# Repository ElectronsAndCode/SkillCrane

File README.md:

This is a schematic diagram with circuit explanations for the Benton Big Choice/Action Crane claw games.

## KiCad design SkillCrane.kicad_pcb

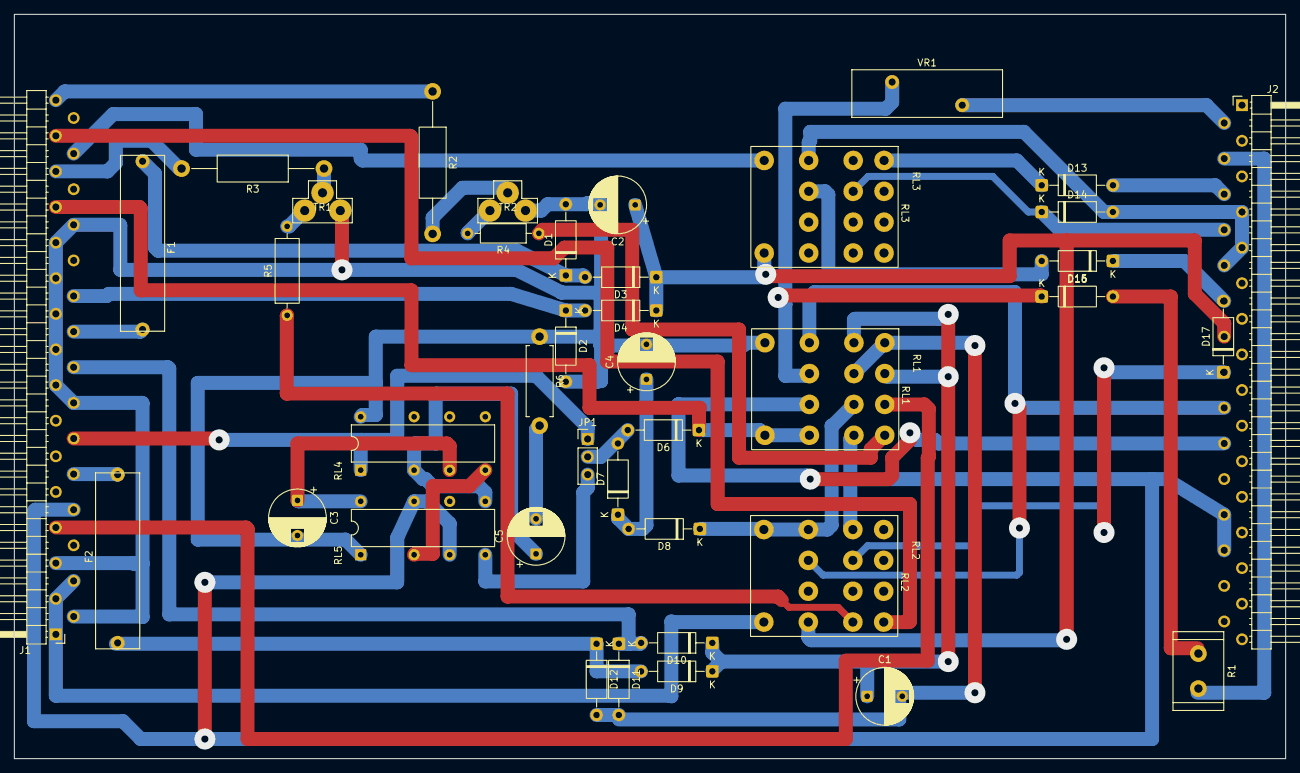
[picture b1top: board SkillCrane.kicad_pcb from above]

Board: 2 copper layers, 181.4 x 106.2 mm, 40 parts (0 on the bottom side), 46 nets.

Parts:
C1, C2, C3, C4: CP_Radial_D8.0mm_P5.00mm
C5: 220uF/25V; CP_Radial_D8.0mm_P5.00mm
D1, D2, D3, D4, D6, D7, D8, D9, D10, D11, D12, D16: D; D_A-405_P10.16mm_Horizontal
D13, D14, D15, D17: D_A-405_P10.16mm_Horizontal
F1: 24V 1A; Fuse
F2: 48V 1A; Fuse
J1: PanelPin; Connector
J2: CabinetPin; Connector
JP1: #COINS; PinHeader_1x03_P2.54mm_Vertical
R1: GRAB STRENGTH; R_Radial_Power_L11.0mm_W7.0mm_P5.00mm
R2, R3: R_Axial_DIN0411_L9.9mm_D3.6mm_P20.32mm_Horizontal
R4: R_Axial_DIN0207_L6.3mm_D2.5mm_P10.16mm_Horizontal
R5: R_Axial_DIN0309_L9.0mm_D3.2mm_P12.70mm_Horizontal
R6: 15K; R_Axial_DIN0411_L9.9mm_D3.6mm_P12.70mm_Horizontal
RL1, RL2, RL3: Relay; PY4-Omron
RL4, RL5: Relay; G2VN
TR1: ZW; Triac
TR2: VW; Triac
VR1: Varistor; RV_Disc_D21.5mm_W6.8mm_P10mm

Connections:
+24V: C2.1, D3.1 (K), D4.1 (K), J2.14, RL2.9, RL3.14
GND: C2.2, C3.2, C4.2, D1.2 (A), D2.2 (A), J1.2, J1.5, J1.14, J1.15, J1.17, J1.19, J1.21, J1.23, J1.24, R6.1, RL1.13, RL4.8, RL5.1, TR1.1 (A1), TR2.1 (A1)
unnamed: C3.1, RL4.3, RL5.8
unnamed: C5.1, RL4.2, RL5.5
unnamed: C5.2, R6.2
unnamed: D1.1 (K), D3.2 (A), F1.1
unnamed: D2.1 (K), D4.2 (A), J1.20
unnamed: D6.2 (A), D7.2 (A), JP1.2 (C)
unnamed: D6.1 (K), J1.25, RL1.9, RL1.14
unnamed: C4.1, D7.1 (K), D8.2 (A)
unnamed: D8.1 (K), RL1.6, RL2.12, RL2.13
unnamed: D10.2 (A), D11.1 (K), J1.16
unnamed: C1.1, D9.1 (K), D10.1 (K), RL1.3, RL1.8
unnamed: C1.2, D11.2 (A), D12.2 (A), RL1.4, RL1.7
unnamed: D9.2 (A), D12.1 (K), F2.1
unnamed: D13.2 (A), J2.6
unnamed: D13.1 (K), RL3.4
unnamed: D14.2 (A), J2.7, J2.9, J2.10, RL3.12
unnamed: D14.1 (K), J2.8, RL3.7
unnamed: D15.2 (A), RL3.11
unnamed: D15.1 (K), D17.2 (A), J2.12
unnamed: D16.2 (A), R1.1
unnamed: D16.1 (K), RL1.11, VR1.2
unnamed: D17.1 (K), J2.16, RL2.7
unnamed: F2.2, J1.10
unnamed: F1.2, J1.18
unnamed: J1.28, RL3.13
unnamed: J1.8, J2.24, J2.26, RL1.5, RL2.8, RL5.3, RL5.7
unnamed: J1.12, JP1.1 (A), RL4.1
unnamed: J1.27, R3.2
unnamed: J1.7, RL1.2
unnamed: J1.29, RL2.1
unnamed: J1.31, R2.1
unnamed: J1.1, J1.3, J1.4, RL2.14
unnamed: J2.20, RL1.10
unnamed: J2.18, RL1.12, RL2.11
unnamed: J2.2, VR1.1
unnamed: J2.4, R1.2
unnamed: JP1.3 (B), RL5.4
unnamed: R4.1, RL1.1
unnamed: R5.1, RL2.5
unnamed: RL4.4, RL5.2
unnamed: R3.1, TR1.2 (A2)
unnamed: R5.2, TR1.3 (G)
unnamed: R2.2, TR2.2 (A2)
unnamed: R4.2, TR2.3 (G)
